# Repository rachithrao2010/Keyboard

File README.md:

This is my MIDI keyboard!
It comes with 8 keyts, 2 octave shift keys, and needs to connect to a computer to work. Left octave shift to go down and right to go up an octave!

I made it with KiCAD for the pcb and Onshape for the enclosure.
It works pretty simple, with  each key being a capacitive touch, and then triggers an interrupt to tell the computer to play a specific note!

PCB:

Render:

Enclosure:

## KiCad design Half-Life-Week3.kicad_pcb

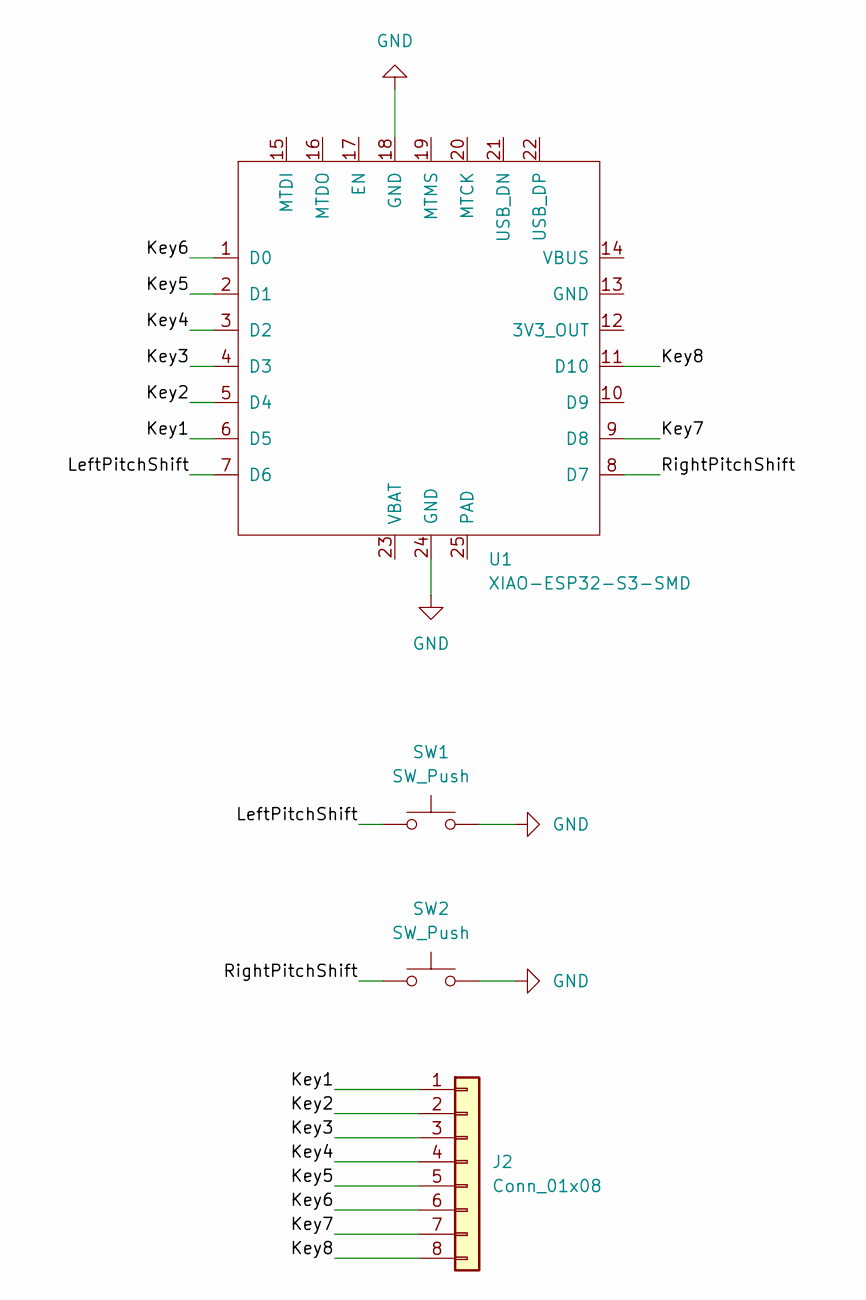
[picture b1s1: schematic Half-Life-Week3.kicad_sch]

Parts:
J2: Conn_01x08; Untitled
SW1, SW2: SW_Push; SW_PUSH_6mm
U1: XIAO-ESP32-S3-SMD; SeeedStudio_XIAO_ESP32S3

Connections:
/Key1: J2.1, U1.6 (D5)
/Key2: J2.2, U1.5 (D4)
/Key3: J2.3, U1.4 (D3)
/Key4: J2.4, U1.3 (D2)
/Key5: J2.5, U1.2 (D1)
/Key6: J2.6, U1.1 (D0)
/Key7: J2.7, U1.9 (D8)
/Key8: J2.8, U1.11 (D10)
/LeftPitchShift: SW1.1, U1.7 (D6)
/RightPitchShift: SW2.1, U1.8 (D7)
GND: SW1.2, SW2.2, U1.18 (GND), U1.24 (GND)

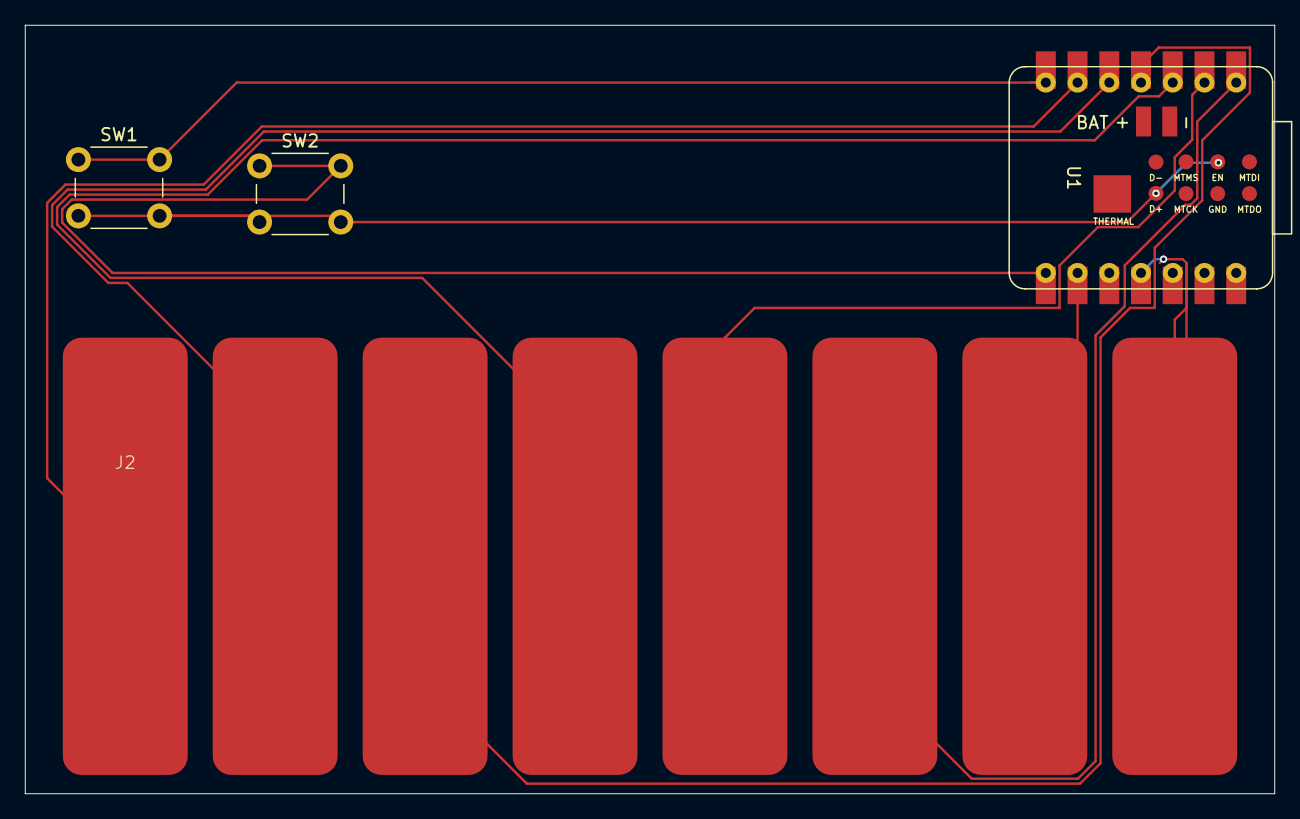
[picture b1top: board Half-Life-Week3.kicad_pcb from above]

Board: 2 copper layers, 100.0 x 61.5 mm, 4 parts (0 on the bottom side), 11 nets.
